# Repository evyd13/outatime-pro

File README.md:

# Outatime Pro
A PCB for Casio CA-53W or 3208 module based on the [Sensor Watch Pro](https://github.com/joeycastillo/Sensor-Watch). It has the same features!

# Firmware
Firmware is being worked on [here](https://github.com/evyd13/second-movement/tree/outatime-pro).

# WARNING
THIS IS NOT TESTED IN ANY WAY. DO NOT ORDER THIS THINKING IT WILL WORK. FIRMWARE DOESN'T EXIST FOR IT YET. IT IS A WORK IN PROGRESS.
However, the PCB design is done.

## Version number
Version number is date formate yyMMDD, August 25th 2026 would be v260825.

# To-Do
The following still needs work:

- Firmware needs to be finished (work has started!)
- figure out if the selection signals for PAM8904 need to be connected to GPIO or always HIGH.
- PCB needs to be ordered and tested (I intend to do this in a few months time, need to gather funds for a prototype)
- It needs to be worn and loved!!

# Bootloader
I contacted devolov, they said to me that the firmware needs to be flashed with utils/flash_watch_pyruler using Adafruit PyRuler or Trinket. (I intend to use Seeed XIAO or maybe Pi Pico.)

Bootloader.h is generated from https://github.com/joeycastillo/uf2-samdx1.
There is an issue with building the bootloader, please see [this](https://github.com/joeycastillo/second-movement/issues/182) issue. 
(Thanks @devolov!)

# LCD
The LCD is fairly simple. It has 35 pins, of which the leftmost is not connected. The first 3 connected pins are common, the rest are segments. Mapping can be found within the emulator svg file or watch_common_display.h. (Seg08 and seg01 are swapped in software to allow blinking)

# Thanks to and relevant projects
- Joey Castillo for Sensor Watch, which this project is mostly based on. https://github.com/joeycastillo/Sensor-Watch/tree/main
- Travis Goodspeed, for incredible documentation about the Casio CA-53W. https://github.com/travisgoodspeed/goodwatch
- Vasily Zhuravsky, for a nice USB edge connector library https://github.com/vasya-zh/PCB-Edge-USB-connector-KiCad-library
- Dmitry Teplitsky, for making me think I can do it https://github.com/icelord75/icesio
- Greg Davill, for pointing the way to a microcontroller to use. https://github.com/gregdavill/advent-calendar-of-circuits-2020/tree/main/arm-watch

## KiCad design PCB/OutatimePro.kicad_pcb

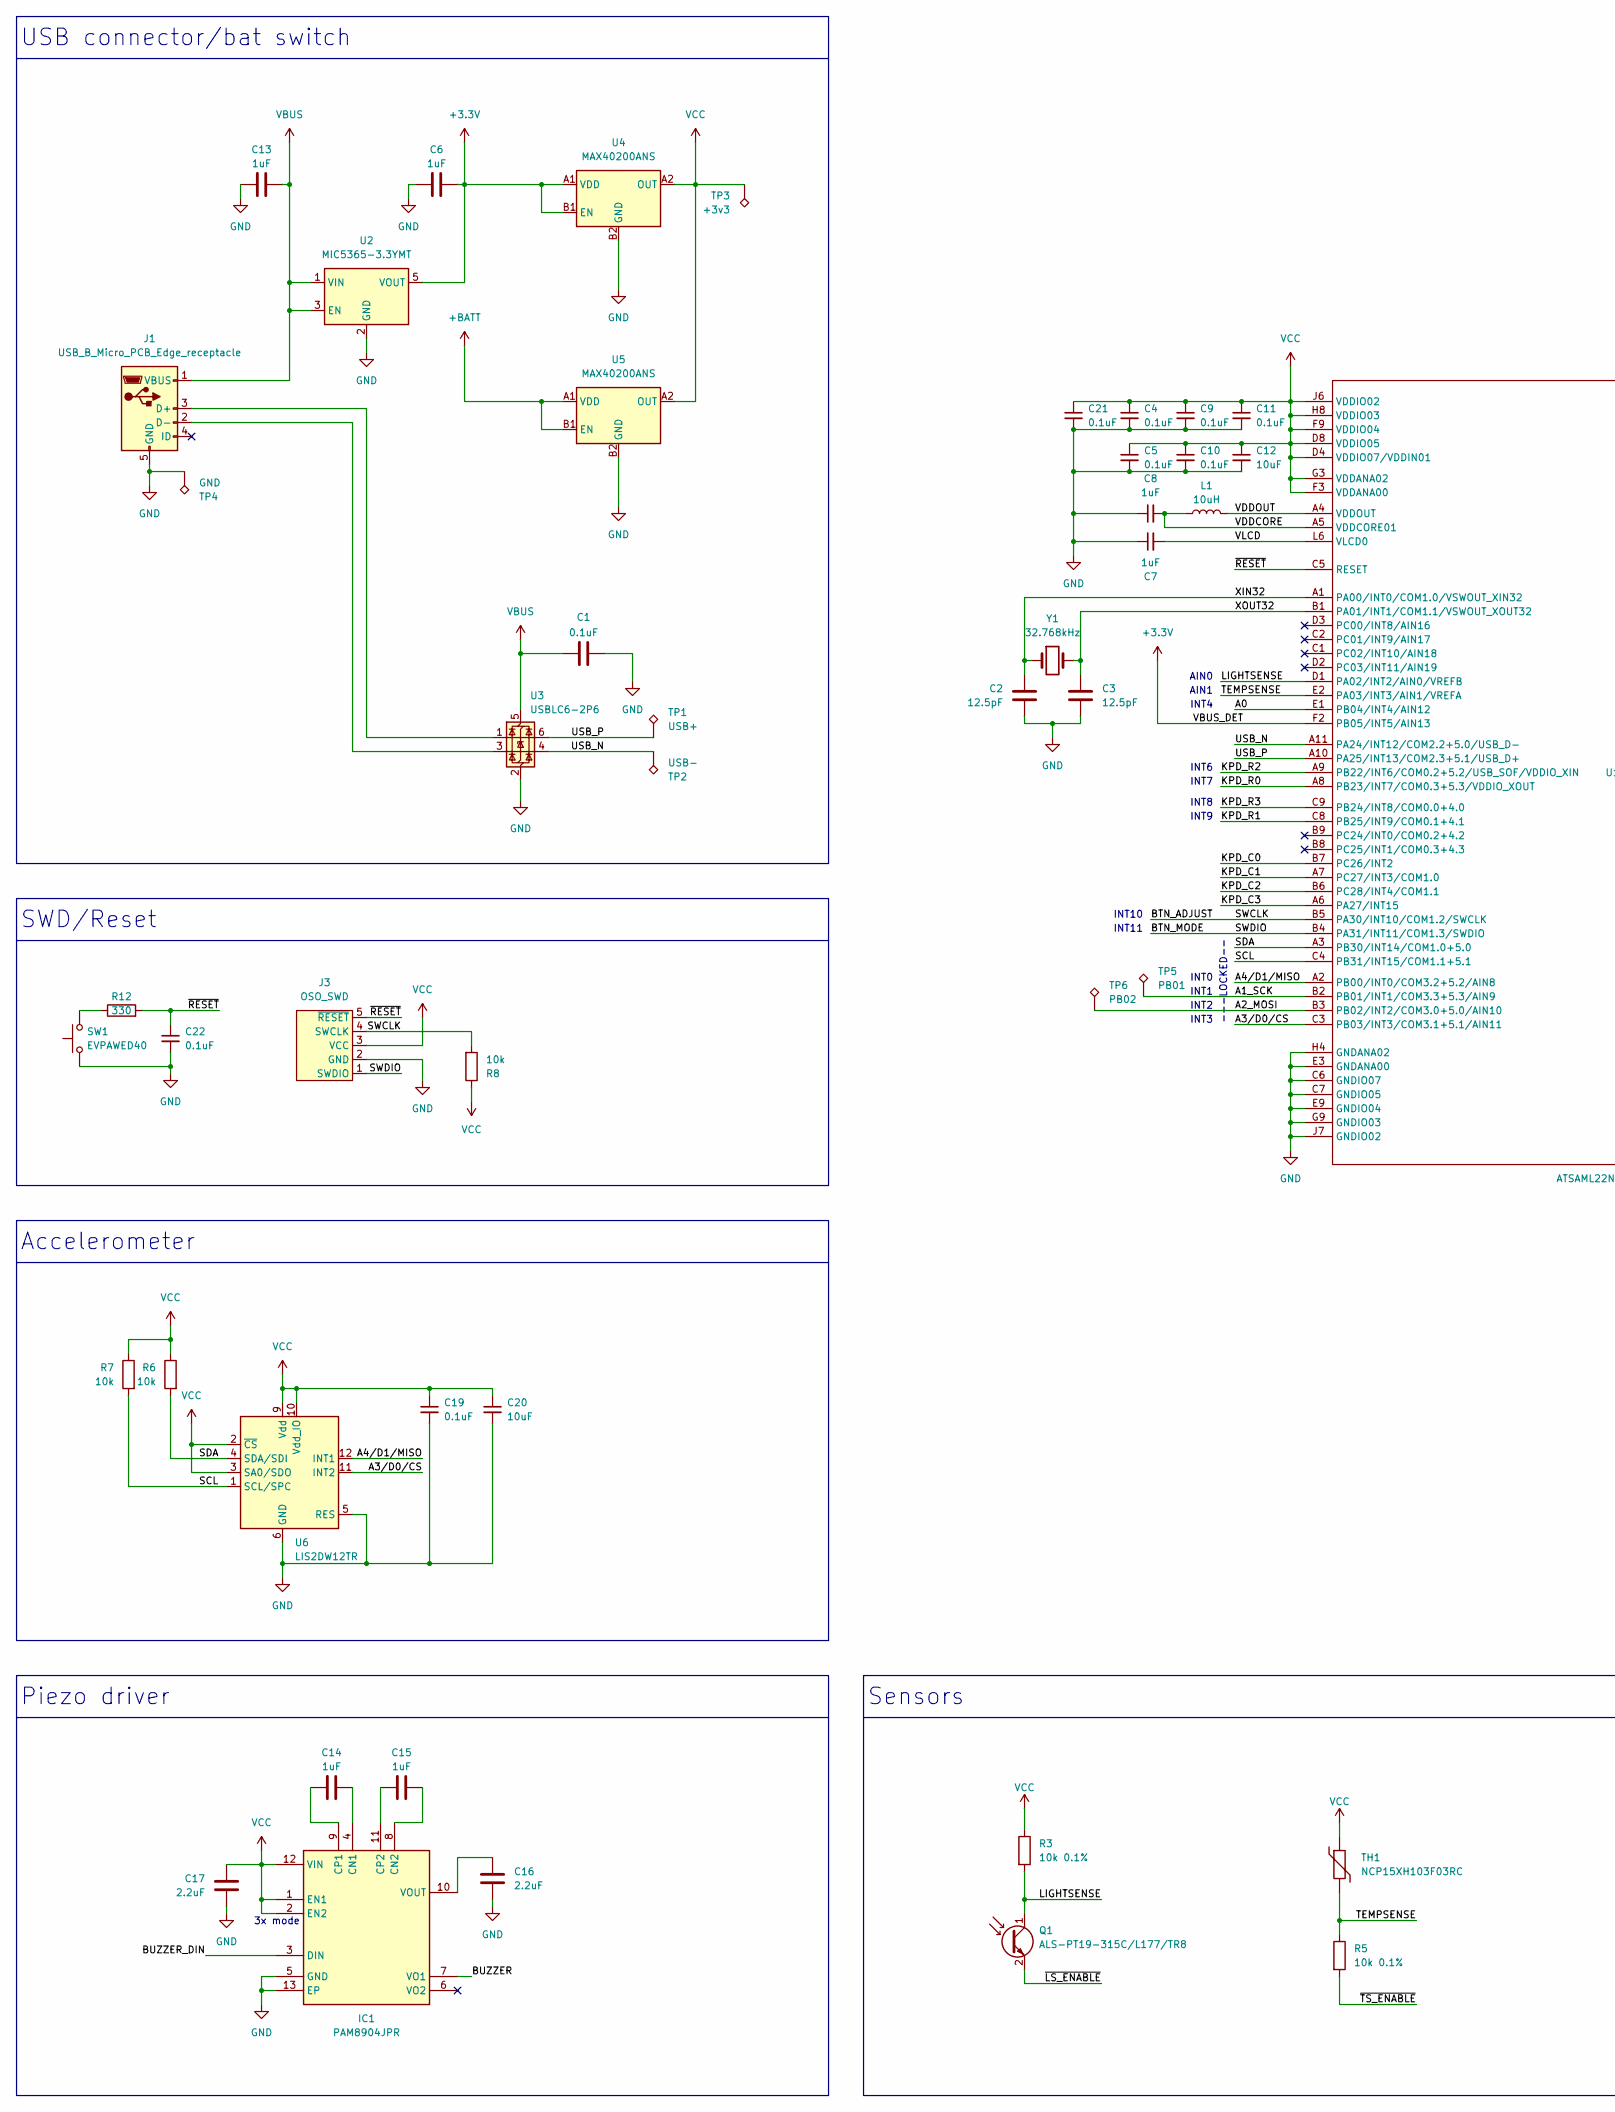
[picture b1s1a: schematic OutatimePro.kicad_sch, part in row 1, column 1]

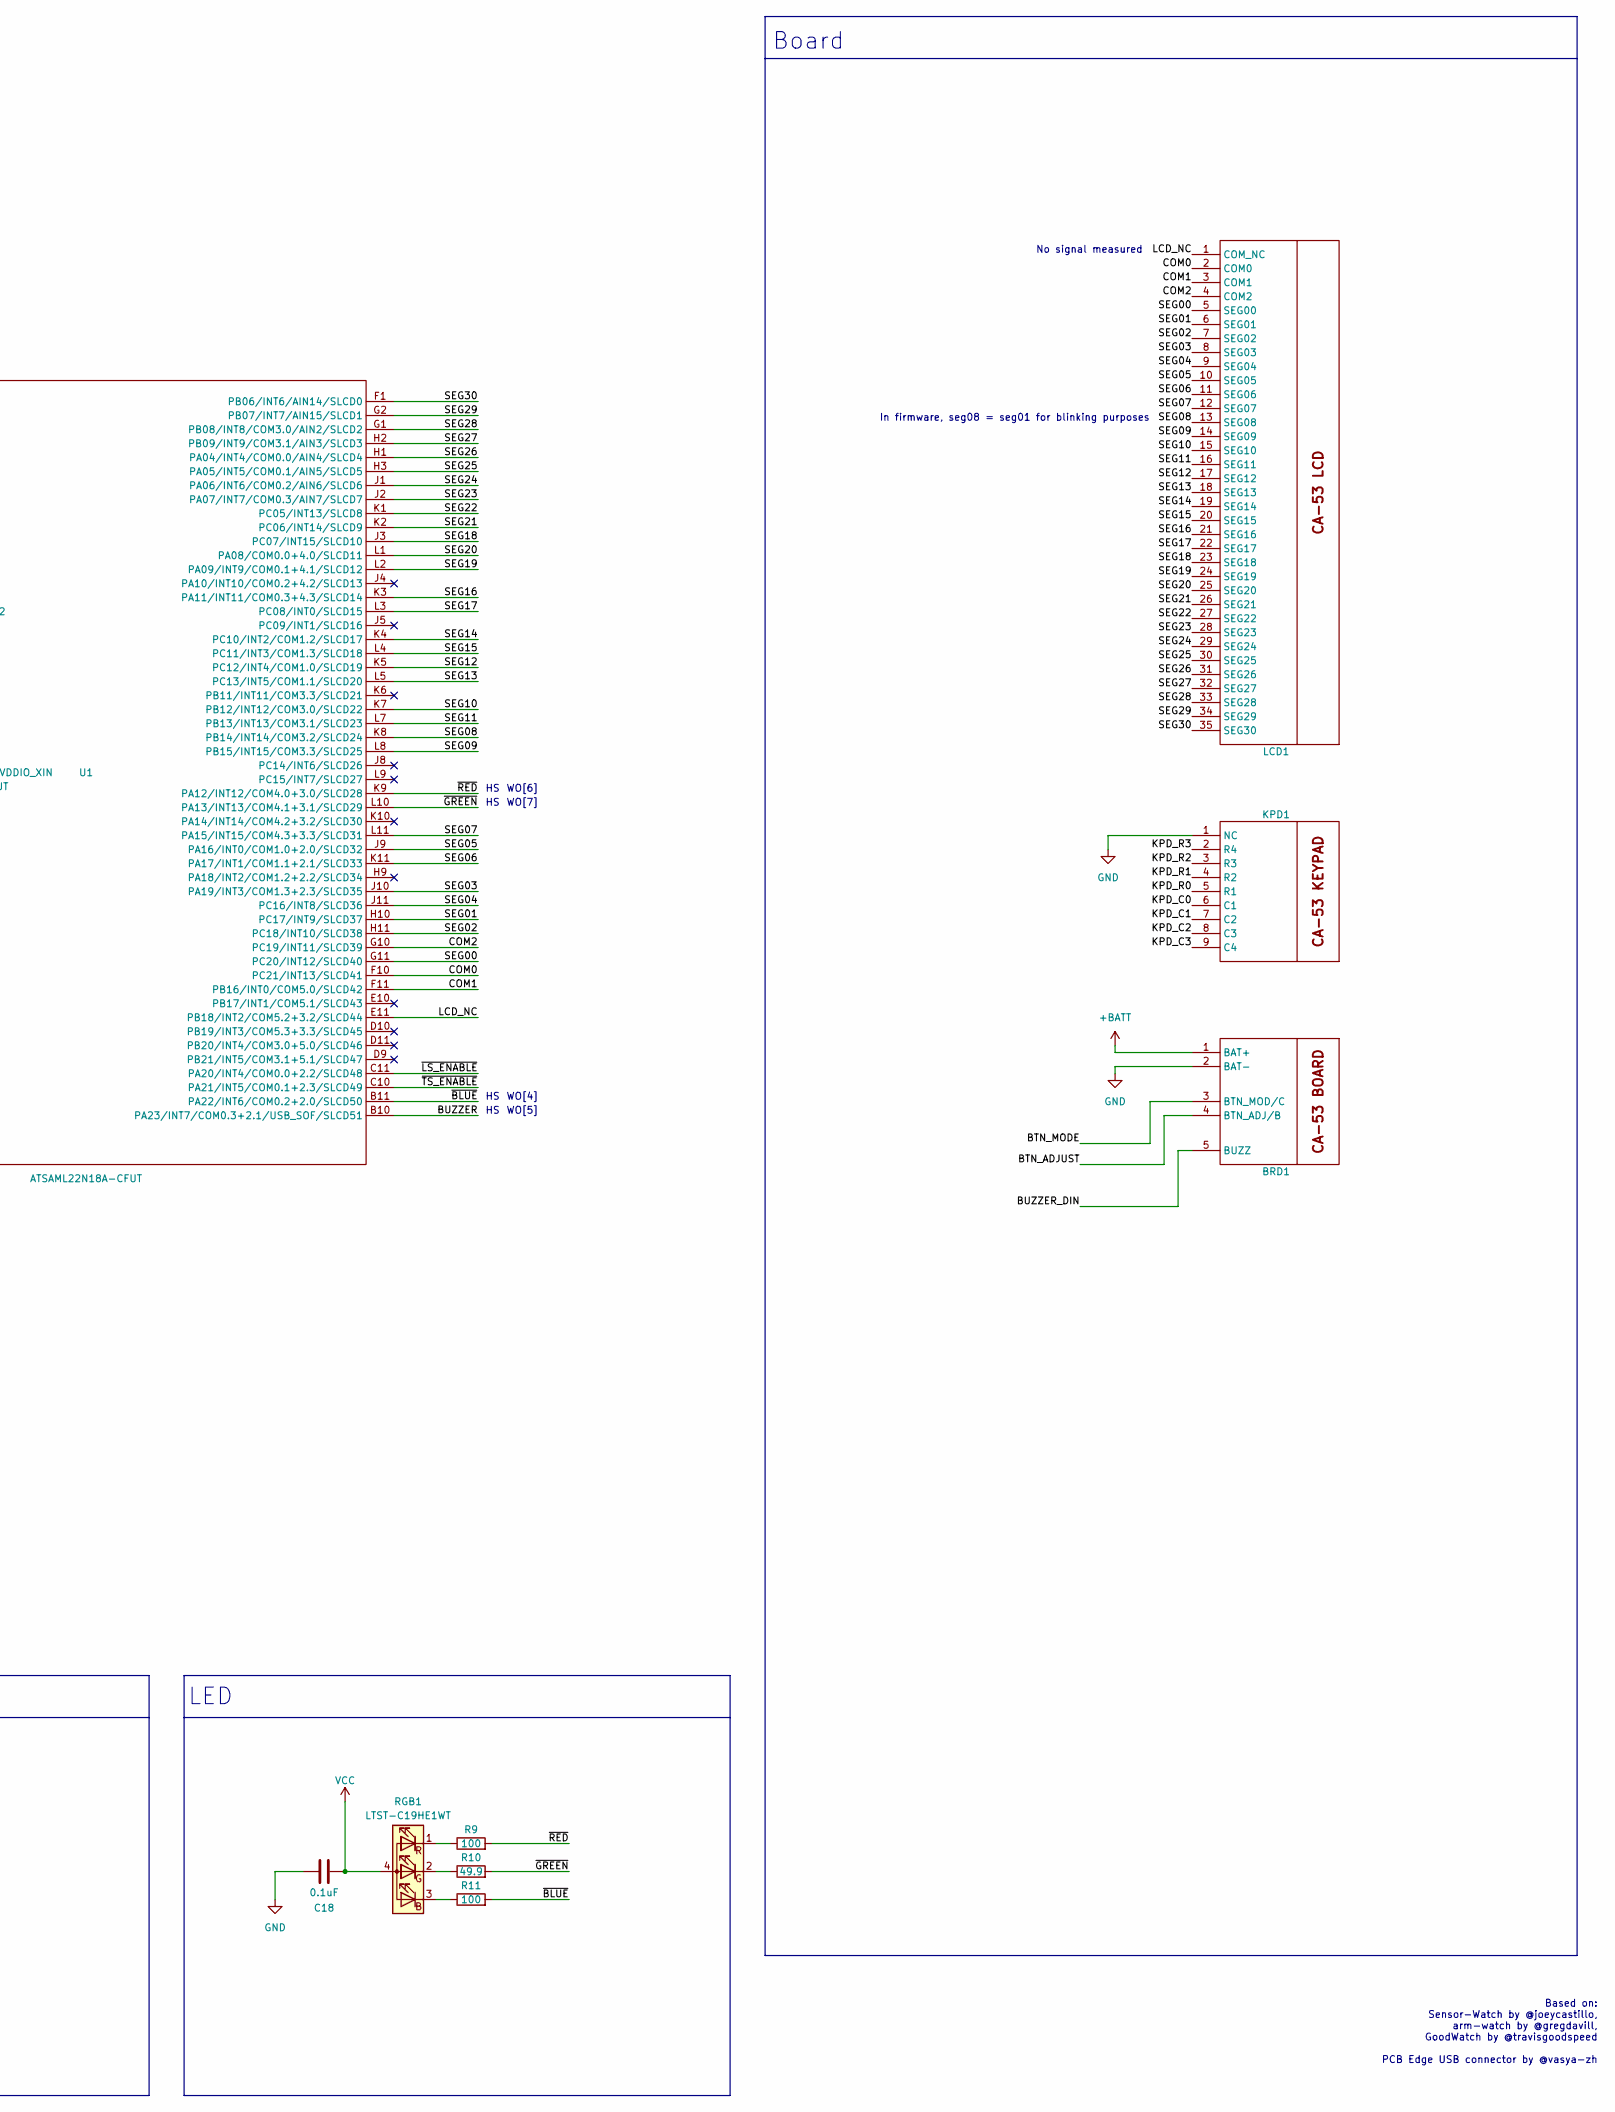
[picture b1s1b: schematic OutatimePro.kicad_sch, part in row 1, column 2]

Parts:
BRD1: ca53board
C1, C4, C5, C9, C10, C11, C18, C19, C21, C22: 0.1uF; C_0402_1005Metric; LCSC Part # C1525
C2, C3: 12.5pF; C_0402_1005Metric; LCSC Part # C1547
C6, C7, C8, C13, C14, C15: 1uF; C_0402_1005Metric; LCSC Part # C52923
C12, C20: 10uF; C_0603_1608Metric; LCSC Part # C19702
C16, C17: 2.2uF; C_0402_1005Metric; LCSC Part # C12530
IC1: PAM8904JPR; LCSC Part # C780875
J1: USB_B_Micro_PCB_Edge_receptacle; USB_Micro-B_PCB_receptacle_5pin_2mm_cutout
J3: OSO_SWD; OSO_SWD_2x3
KPD1: ca53keypad
L1: 10uH; L_0603_1608Metric; LCSC Part # C1035
LCD1: ca53lcd
Q1: ALS-PT19-315C/L177/TR8; ALS-PT19-315C; LCSC Part # C146233
R3, R5: 10k 0.1%; R_0402_1005Metric; LCSC Part # C517449
R6, R7, R8: 10k; R_0402_1005Metric; LCSC Part # C25744
R9, R11: 100; R_0402_1005Metric; LCSC Part # C25076
R10: 49.9; R_0402_1005Metric; LCSC Part # C25120
R12: 330; R_0402_1005Metric; LCSC Part # C25104
RGB1: LTST-C19HE1WT; LED_LiteOn_LTST-C19HE1WT; LCSC Part # C458749
SW1: EVPAWED40; Panasonic_EVPAW_EVP6A; LCSC Part # C2858607
TH1: NCP15XH103F03RC; TH_0402_1005Metric; LCSC Part # C77131
TP1: USB+; TestPoint_Pad_D1.0mm
TP2: USB-; TestPoint_Pad_D1.0mm
TP3: +3v3; TestPoint_Pad_D1.0mm
TP4: GND; TestPoint_Pad_D1.0mm
TP5: PB01; TestPoint_Pad_D1.0mm
TP6: PB02; TestPoint_Pad_D1.0mm
U1: ATSAML22N18A-CFUT; UFBGA-100_6.0x6.0mm_Layout11x11_P0.5mm_Ball0.3mm_Pad0.25mm_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; LCSC Part # C2055605
U2: MIC5365-3.3YMT; UDFN-4-1EP_1x1mm_P0.65mm_EP0.48x0.48mm; LCSC Part # C512103
U3: USBLC6-2P6; SOT-666; LCSC Part # C15999
U4, U5: MAX40200ANS; WLP-4_0.728x0.728mm_Layout2x2_P0.35mm; LCSC Part # C3227637
U6: LIS2DW12TR; LGA-12_2x2mm_P0.5mm; LCSC Part # C189624
Y1: 32.768kHz; Crystal_SMD_1610-2Pin_1.6x1.0mm; LCSC Part # C5154201

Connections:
+3.3V: C6.2, U1.F2 (PB05/INT5/AIN13), U2.5 (VOUT), U4.A1 (VDD), U4.B1 (EN)
+BATT: BRD1.1 (BAT+), U5.A1 (VDD), U5.B1 (EN)
/A0: U1.E1 (PB04/INT4/AIN12)
/A1_SCK: TP5.1 (1_1), U1.B2 (PB01/INT1/COM3.3+5.3/AIN9)
/A2_MOSI: TP6.1 (1_1), U1.B3 (PB02/INT2/COM3.0+5.0/AIN10)
/A3/D0/CS: U1.C3 (PB03/INT3/COM3.1+5.1/AIN11), U6.11 (INT2)
/A4/D1/MISO: U1.A2 (PB00/INT0/COM3.2+5.2/AIN8), U6.12 (INT1)
/BTN_ADJUST: BRD1.4 (BTN_ADJ/B), J3.4 (SWCLK), R8.2, U1.B5 (PA30/INT10/COM1.2/SWCLK)
/BTN_MODE: BRD1.3 (BTN_MOD/C), J3.1 (SWDIO), U1.B4 (PA31/INT11/COM1.3/SWDIO)
/BUZZER: IC1.7 (VO1), U1.B10 (PA23/INT7/COM0.3+2.1/USB_SOF/SLCD51)
/BUZZER_DIN: BRD1.5 (BUZZ), IC1.3 (DIN)
/COM0: LCD1.2 (COM0), U1.F10 (PC21/INT13/SLCD41)
/COM1: LCD1.3 (COM1), U1.F11 (PB16/INT0/COM5.0/SLCD42)
/COM2: LCD1.4 (COM2), U1.G10 (PC19/INT11/SLCD39)
/KPD_C0: KPD1.6 (C1), U1.B7 (PC26/INT2)
/KPD_C1: KPD1.7 (C2), U1.A7 (PC27/INT3/COM1.0)
/KPD_C2: KPD1.8 (C3), U1.B6 (PC28/INT4/COM1.1)
/KPD_C3: KPD1.9 (C4), U1.A6 (PA27/INT15)
/KPD_R0: KPD1.5 (R1), U1.A8 (PB23/INT7/COM0.3+5.3/VDDIO_XOUT)
/KPD_R1: KPD1.4 (R2), U1.C8 (PB25/INT9/COM0.1+4.1)
/KPD_R2: KPD1.3 (R3), U1.A9 (PB22/INT6/COM0.2+5.2/USB_SOF/VDDIO_XIN)
/KPD_R3: KPD1.2 (R4), U1.C9 (PB24/INT8/COM0.0+4.0)
/LCD_NC: LCD1.1 (COM_NC), U1.E11 (PB18/INT2/COM5.2+3.2/SLCD44)
/LIGHTSENSE: Q1.1 (C), R3.2, U1.D1 (PA02/INT2/AIN0/VREFB)
/SCL: R7.2, U1.C4 (PB31/INT15/COM1.1+5.1), U6.1 (SCL/SPC)
/SDA: R6.2, U1.A3 (PB30/INT14/COM1.0+5.0), U6.4 (SDA/SDI)
/SEG00: LCD1.5 (SEG00), U1.G11 (PC20/INT12/SLCD40)
/SEG01: LCD1.6 (SEG01), U1.H10 (PC17/INT9/SLCD37)
/SEG02: LCD1.7 (SEG02), U1.H11 (PC18/INT10/SLCD38)
/SEG03: LCD1.8 (SEG03), U1.J10 (PA19/INT3/COM1.3+2.3/SLCD35)
/SEG04: LCD1.9 (SEG04), U1.J11 (PC16/INT8/SLCD36)
/SEG05: LCD1.10 (SEG05), U1.J9 (PA16/INT0/COM1.0+2.0/SLCD32)
/SEG06: LCD1.11 (SEG06), U1.K11 (PA17/INT1/COM1.1+2.1/SLCD33)
/SEG07: LCD1.12 (SEG07), U1.L11 (PA15/INT15/COM4.3+3.3/SLCD31)
/SEG08: LCD1.13 (SEG08), U1.K8 (PB14/INT14/COM3.2/SLCD24)
/SEG09: LCD1.14 (SEG09), U1.L8 (PB15/INT15/COM3.3/SLCD25)
/SEG10: LCD1.15 (SEG10), U1.K7 (PB12/INT12/COM3.0/SLCD22)
/SEG11: LCD1.16 (SEG11), U1.L7 (PB13/INT13/COM3.1/SLCD23)
/SEG12: LCD1.17 (SEG12), U1.K5 (PC12/INT4/COM1.0/SLCD19)
/SEG13: LCD1.18 (SEG13), U1.L5 (PC13/INT5/COM1.1/SLCD20)
/SEG14: LCD1.19 (SEG14), U1.K4 (PC10/INT2/COM1.2/SLCD17)
/SEG15: LCD1.20 (SEG15), U1.L4 (PC11/INT3/COM1.3/SLCD18)
/SEG16: LCD1.21 (SEG16), U1.K3 (PA11/INT11/COM0.3+4.3/SLCD14)
/SEG17: LCD1.22 (SEG17), U1.L3 (PC08/INT0/SLCD15)
/SEG18: LCD1.23 (SEG18), U1.J3 (PC07/INT15/SLCD10)
/SEG19: LCD1.24 (SEG19), U1.L2 (PA09/INT9/COM0.1+4.1/SLCD12)
/SEG20: LCD1.25 (SEG20), U1.L1 (PA08/COM0.0+4.0/SLCD11)
/SEG21: LCD1.26 (SEG21), U1.K2 (PC06/INT14/SLCD9)
/SEG22: LCD1.27 (SEG22), U1.K1 (PC05/INT13/SLCD8)
/SEG23: LCD1.28 (SEG23), U1.J2 (PA07/INT7/COM0.3/AIN7/SLCD7)
/SEG24: LCD1.29 (SEG24), U1.J1 (PA06/INT6/COM0.2/AIN6/SLCD6)
/SEG25: LCD1.30 (SEG25), U1.H3 (PA05/INT5/COM0.1/AIN5/SLCD5)
/SEG26: LCD1.31 (SEG26), U1.H1 (PA04/INT4/COM0.0/AIN4/SLCD4)
/SEG27: LCD1.32 (SEG27), U1.H2 (PB09/INT9/COM3.1/AIN3/SLCD3)
/SEG28: LCD1.33 (SEG28), U1.G1 (PB08/INT8/COM3.0/AIN2/SLCD2)
/SEG29: LCD1.34 (SEG29), U1.G2 (PB07/INT7/AIN15/SLCD1)
/SEG30: LCD1.35 (SEG30), U1.F1 (PB06/INT6/AIN14/SLCD0)
/TEMPSENSE: R5.1, TH1.2, U1.E2 (PA03/INT3/AIN1/VREFA)
/USB_N: TP2.1 (1_1), U1.A11 (PA24/INT12/COM2.2+5.0/USB_D-), U3.4 (I/O2)
/USB_P: TP1.1 (1_1), U1.A10 (PA25/INT13/COM2.3+5.1/USB_D+), U3.6 (I/O1)
/VDDCORE: C8.2, L1.1, U1.A5 (VDDCORE01)
/VDDOUT: L1.2, U1.A4 (VDDOUT)
/VLCD: C7.2, U1.L6 (VLCD0)
/XIN32: C2.1, U1.A1 (PA00/INT0/COM1.0/VSWOUT_XIN32), Y1.1
/XOUT32: C3.1, U1.B1 (PA01/INT1/COM1.1/VSWOUT_XOUT32), Y1.2
/~BLUE: R11.2, U1.B11 (PA22/INT6/COM0.2+2.0/SLCD50)
/~GREEN: R10.2, U1.L10 (PA13/INT13/COM4.1+3.1/SLCD29)
/~LS_ENABLE: Q1.2 (E), U1.C11 (PA20/INT4/COM0.0+2.2/SLCD48)
/~RED: R9.2, U1.K9 (PA12/INT12/COM4.0+3.0/SLCD28)
/~RESET: C22.1, J3.5 (~RESET), R12.2, U1.C5 (RESET)
/~TS_ENABLE: R5.2, U1.C10 (PA21/INT5/COM0.1+2.3/SLCD49)
GND: BRD1.2 (BAT-), C1.2, C2.2, C3.2, C4.2, C5.2, C6.1, C7.1, C8.1, C9.2, C10.2, C11.2, C12.2, C13.1, C16.1, C17.1, C18.1, C19.2, C20.2, C21.2, C22.2, IC1.5 (GND), IC1.13 (EP), J1.5 (GND), J3.2 (GND), KPD1.1 (NC), SW1.1, TP4.1 (1_1), U1.C6 (GNDIO07), U1.C7 (GNDIO05), U1.E3 (GNDANA00), U1.E9 (GNDIO04), U1.G9 (GNDIO03), U1.H4 (GNDANA02), U1.J7 (GNDIO02), U2.2 (GND), U3.2 (GND), U4.B2 (GND), U5.B2 (GND), U6.5 (RES), U6.6 (GND), U6.7 (GND), U6.8 (GND)
unnamed: C14.2, IC1.4 (CN1)
unnamed: C15.2, IC1.8 (CN2)
unnamed: C14.1, IC1.9 (CP1)
unnamed: C15.1, IC1.11 (CP2)
unnamed: C16.2, IC1.10 (VOUT)
unnamed: J1.3 (D+), U3.1 (I/O1)
unnamed: J1.2 (D-), U3.3 (I/O2)
unnamed: R12.1, SW1.2
unnamed: R11.1, RGB1.3 (BK)
unnamed: R10.1, RGB1.2 (GK)
unnamed: R9.1, RGB1.1 (RK)
VBUS: C1.1, C13.2, J1.1 (VBUS), U2.1 (VIN), U2.3 (EN), U3.5 (VBUS)
VCC: C4.1, C5.1, C9.1, C10.1, C11.1, C12.1, C17.2, C18.2, C19.1, C20.1, C21.1, IC1.1 (EN1), IC1.2 (EN2), IC1.12 (VIN), J3.3 (VCC), R3.1, R6.1, R7.1, R8.1, RGB1.4 (A), TH1.1, TP3.1 (1_1), U1.D4 (VDDIO07/VDDIN01), U1.D8 (VDDIO05), U1.F3 (VDDANA00), U1.F9 (VDDIO04), U1.G3 (VDDANA02), U1.H8 (VDDIO03), U1.J6 (VDDIO02), U4.A2 (OUT), U5.A2 (OUT), U6.2 (~CS), U6.3 (SA0/SDO), U6.9 (Vdd), U6.10 (Vdd_IO)

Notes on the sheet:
INT0
Piezo driver
INT2
WO[6]
SWD/Reset
WO[4]
Board
INT1
INT8
INT11
INT10
WO[7]
INT3
Sensors
---LOCKED--
USB connector/bat switch
INT7
INT9
3x mode
LED
No signal measured
INT4
Accelerometer
AIN0
WO[5]
Based on: Sensor-Watch by @joeycastillo, arm-watch by @gregdavill, GoodWatch by @travisgoodspeed PCB Edge USB connector by @vasya-zh
INT6
AIN1
In firmware, seg08 = seg01 for blinking purposes

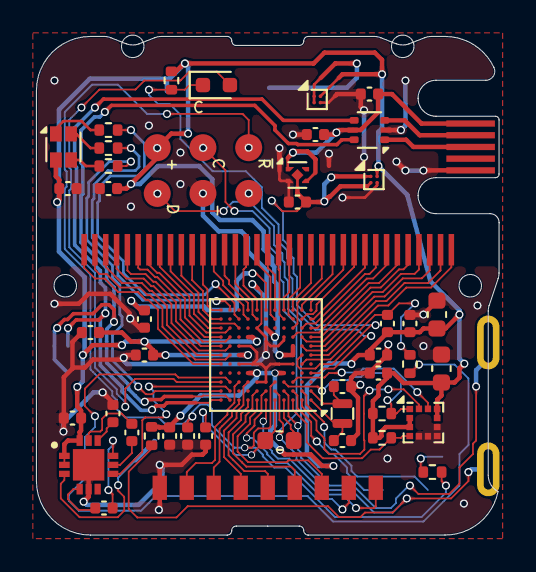
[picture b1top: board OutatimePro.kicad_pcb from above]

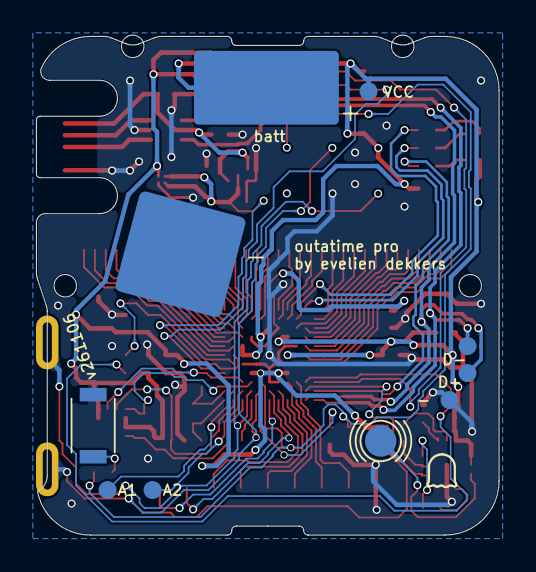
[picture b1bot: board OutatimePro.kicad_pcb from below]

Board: 2 copper layers, 25.7 x 27.7 mm, 55 parts (7 on the bottom side), 84 nets.

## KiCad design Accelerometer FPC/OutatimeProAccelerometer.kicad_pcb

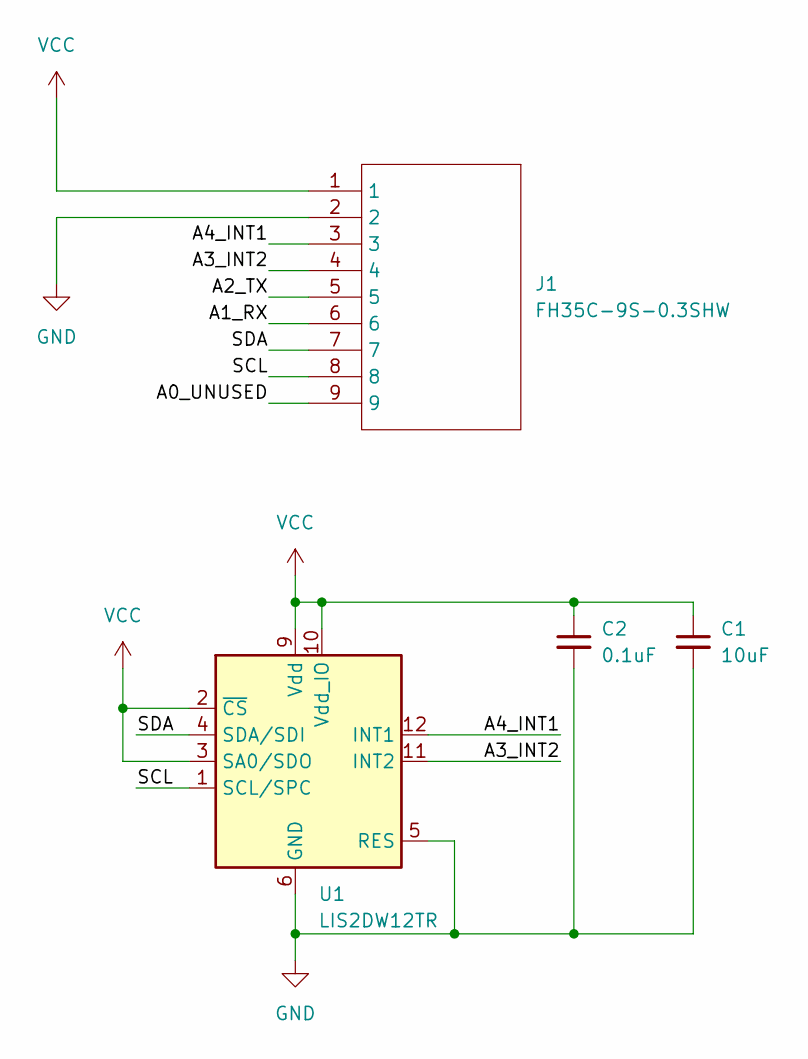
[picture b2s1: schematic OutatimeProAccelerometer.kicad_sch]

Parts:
C1: 10uF; C_0603_1608Metric; LCSC Part # C19702
C2: 0.1uF; C_0402_1005Metric; LCSC Part # C14663
J1: FH35C-9S-0.3SHW; FH35C-9-FPC
U1: LIS2DW12TR; LGA-12_2x2mm_P0.5mm; LCSC Part # C189624

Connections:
/A0_UNUSED: J1.9
/A1_RX: J1.6
/A2_TX: J1.5
/A3_INT2: J1.4, U1.11 (INT2)
/A4_INT1: J1.3, U1.12 (INT1)
/SCL: J1.8, U1.1 (SCL/SPC)
/SDA: J1.7, U1.4 (SDA/SDI)
GND: C1.2, C2.2, J1.2, U1.5 (RES), U1.6 (GND), U1.7 (GND), U1.8 (GND)
VCC: C1.1, C2.1, J1.1, U1.2 (~CS), U1.3 (SA0/SDO), U1.9 (Vdd), U1.10 (Vdd_IO)

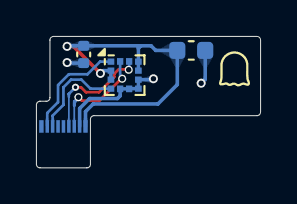
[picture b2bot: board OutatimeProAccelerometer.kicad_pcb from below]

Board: 2 copper layers, 12.4 x 7.3 mm, 4 parts (4 on the bottom side), 6 nets.

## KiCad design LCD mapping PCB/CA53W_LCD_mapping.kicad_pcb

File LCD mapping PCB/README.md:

# For development purposes
This was autorouted, i don't really care for this this one. So I won't spend hours routing or perfecting. It's just to map the LCD and check the fit in the case!

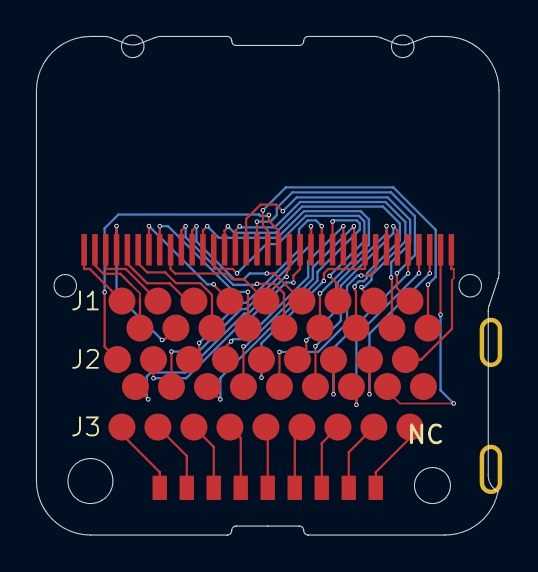
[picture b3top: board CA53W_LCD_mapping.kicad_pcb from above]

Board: 2 copper layers, 25.7 x 27.7 mm, 6 parts (0 on the bottom side), 44 nets.

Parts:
BRD1: ca53board
J1, J2: Conn_01x18; testpads_lcd
J3: Conn_01x09; testpads_keypad
KPD1: ca53keypad
LCD1: ca53lcd

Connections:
/COM0: J1.1, LCD1.1 (COM0)
/COM1: J1.2, LCD1.2 (COM1)
/COM2: J1.3, LCD1.3 (COM2)
/COM3: J1.4, LCD1.4 (COM3)
/KPD_A1: J3.9, KPD1.9 (A1)
/KPD_A2: J3.8, KPD1.8 (A2)
/KPD_A3: J3.7, KPD1.7 (A3)
/KPD_A4: J3.6, KPD1.6 (A4)
/KPD_B1: J3.5, KPD1.5 (B1)
/KPD_B2: J3.4, KPD1.4 (B2)
/KPD_B3: J3.3, KPD1.3 (B3)
/KPD_B4: J3.2, KPD1.2 (B4)
/SEG01: J1.5, LCD1.5 (SEG01)
/SEG02: J1.6, LCD1.6 (SEG02)
/SEG03: J1.7, LCD1.7 (SEG03)
/SEG04: J1.8, LCD1.8 (SEG04)
/SEG05: J1.9, LCD1.9 (SEG05)
/SEG06: J1.10, LCD1.10 (SEG06)
/SEG07: J1.11, LCD1.11 (SEG07)
/SEG08: J1.12, LCD1.12 (SEG08)
/SEG09: J1.13, LCD1.13 (SEG09)
/SEG10: J1.14, LCD1.14 (SEG10)
/SEG11: J1.15, LCD1.15 (SEG11)
/SEG12: J1.16, LCD1.16 (SEG12)
/SEG13: J1.17, LCD1.17 (SEG13)
/SEG14: J1.18, LCD1.18 (SEG14)
/SEG15: J2.1, LCD1.19 (SEG15)
/SEG16: J2.2, LCD1.20 (SEG16)
/SEG17: J2.3, LCD1.21 (SEG17)
/SEG18: J2.4, LCD1.22 (SEG18)
/SEG19: J2.5, LCD1.23 (SEG19)
/SEG20: J2.6, LCD1.24 (SEG20)
/SEG21: J2.7, LCD1.25 (SEG21)
/SEG22: J2.8, LCD1.26 (SEG22)
/SEG23: J2.9, LCD1.27 (SEG23)
/SEG24: J2.10, LCD1.28 (SEG24)
/SEG25: J2.11, LCD1.29 (SEG25)
/SEG26: J2.12, LCD1.30 (SEG26)
/SEG27: J2.13, LCD1.31 (SEG27)
/SEG28: J2.14, LCD1.32 (SEG28)
/SEG29: J2.15, LCD1.33 (SEG29)
/SEG30: J2.16, LCD1.34 (SEG30)
/SEG31: J2.17, LCD1.35 (SEG31)
unnamed: J3.1, KPD1.1 (NC)
